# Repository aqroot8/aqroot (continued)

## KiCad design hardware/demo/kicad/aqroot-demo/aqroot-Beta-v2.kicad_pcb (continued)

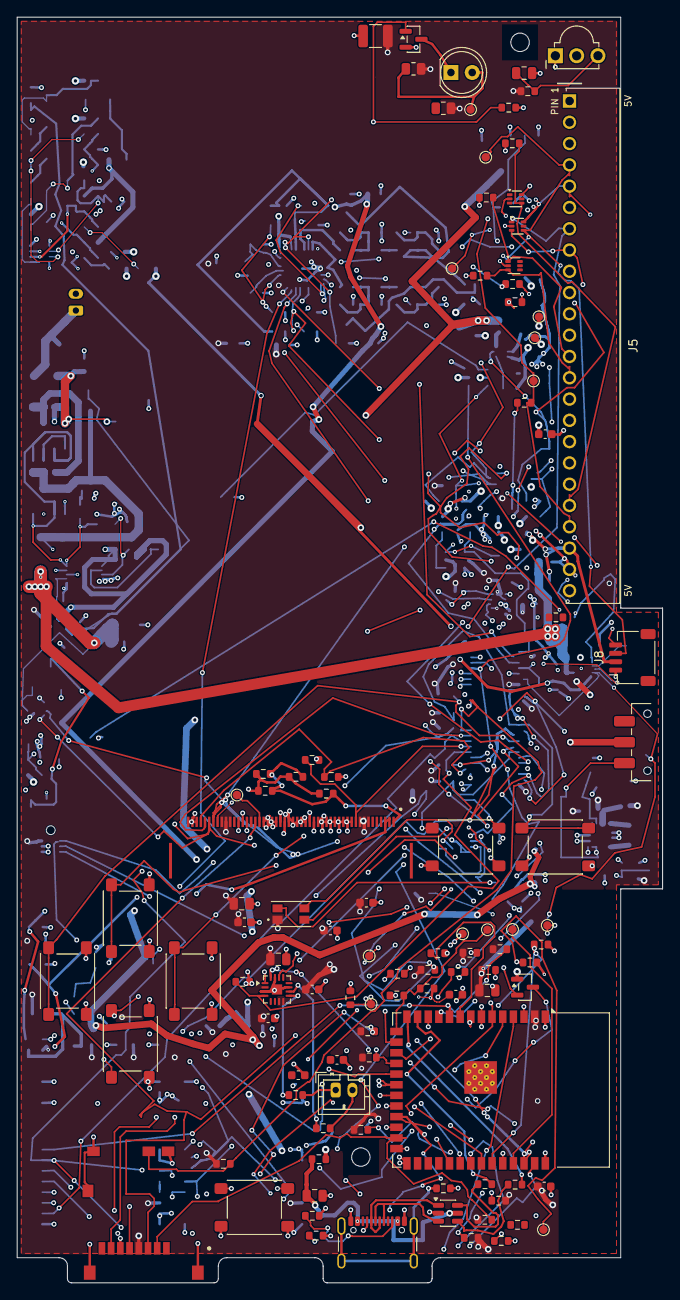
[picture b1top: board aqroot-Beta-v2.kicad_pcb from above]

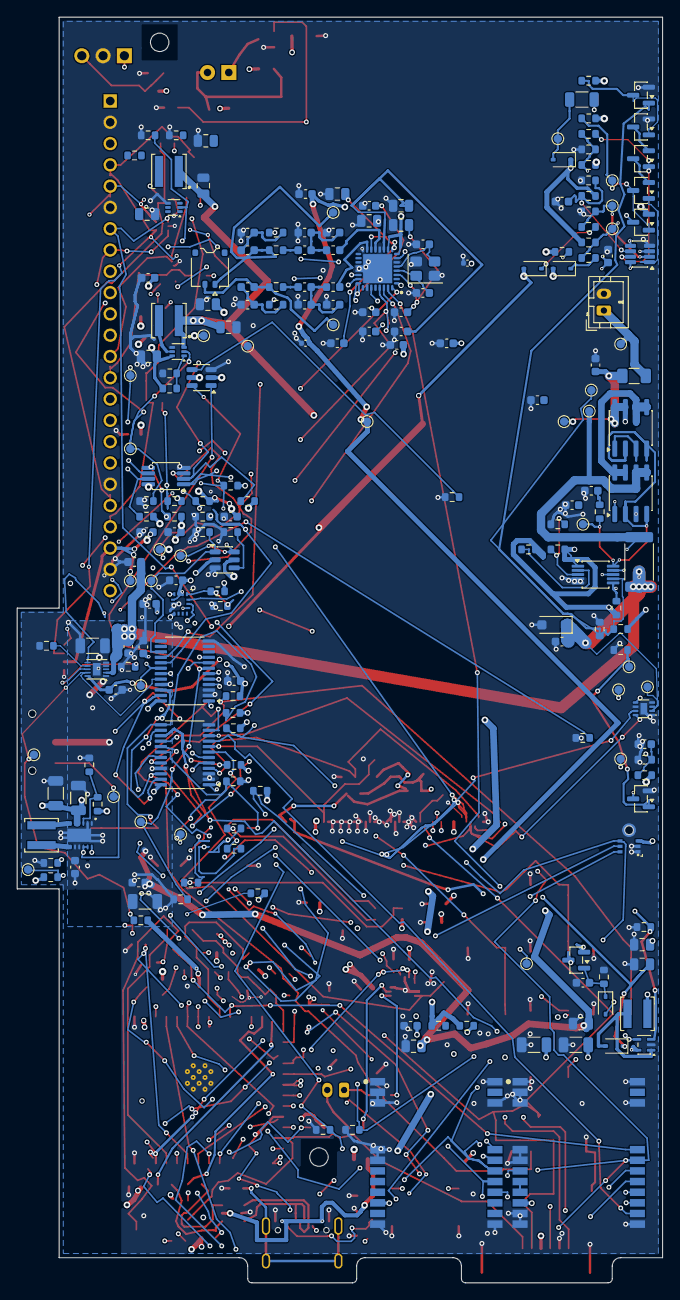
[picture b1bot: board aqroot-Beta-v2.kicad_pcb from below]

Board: 6 copper layers, 77.0 x 151.0 mm, 315 parts (211 on the bottom side), 177 nets.

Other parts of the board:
BOSS1, BOSS2: M2; MountingBoss_M2_NPTH

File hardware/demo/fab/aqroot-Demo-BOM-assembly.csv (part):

"Refs","Value","Footprint","Manufacturer","MPN","LCSC","Description","Qty","DNP"
"C1,C53,C56","1uF","Capacitor_SMD:C_0603_1608Metric","Samsung Electro-Mechanics","CL10A105KB8NNNC","C15849","Unpolarized capacitor","3",""
"C10","10uf","Capacitor_SMD:C_0805_2012Metric","Murata Electronics","GRM21BR61H106KE43L","C440198","Unpolarized capacitor","1",""
"C11","4.7uF","Capacitor_SMD:C_0805_2012Metric","Samsung Electro-Mechanics","CL21A475KAQNNNE","C1779","Unpolarized capacitor","1",""
"C12","22uF","Capacitor_SMD:C_1210_3225Metric","Samsung Electro-Mechanics","CL32B226KAJNNNE","C309062","Unpolarized capacitor","1",""
"C18,C19","100nF","Capacitor_SMD:C_0402_1005Metric","YAGEO","CC0402KRX7R8BB104","C105883","Unpolarized capacitor","2",""
"C2,C4,C5,C6,C7,C8,C9,C13,C14,C16,C17","100nF","Capacitor_SMD:C_0603_1608Metric","YAGEO","CC0603KRX7R9BB104","C14663","Unpolarized capacitor","11",""
"C20","4.7uF 10V X7R","Capacitor_SMD:C_0805_2012Metric","YAGEO","CC0805KKX7R8BB475","C354262","Unpolarized capacitor","1",""
"C23,C58,C59","1uF 25V X7R","Capacitor_SMD:C_0603_1608Metric","YAGEO","CC0603KRX7R8BB105","C106858","Unpolarized capacitor","3",""
"C24","10uF 25V X5R","Capacitor_SMD:C_0603_1608Metric","Murata","GRM188R61E106KA73D","C344022","Unpolarized capacitor","1",""
"C25,C37,C38,C62,C63,C67,C85","1uF 10V X7R","Capacitor_SMD:C_0603_1608Metric","YAGEO","CC0603KRX7R8BB105","C106858","Unpolarized capacitor","7",""
"C26,C27","10uF 10V X7R","Capacitor_SMD:C_1206_3216Metric","Murata Electronics","GRM31CR71E106KA12L","C77093","Unpolarized capacitor","2",""
"C28,C36,C39,C60,C61,C68","100nF X7R","Capacitor_SMD:C_0603_1608Metric","YAGEO","CC0603KRX7R9BB104","C14663","Unpolarized capacitor","6",""
"C29,C30,C31,C32","22uF 16V X7R","Capacitor_SMD:C_1206_3216Metric","CCTC","TCC1206X7R226K160HT","C22392398","Unpolarized capacitor","4",""
"C3,C15","10uF","Capacitor_SMD:C_0805_2012Metric","Murata Electronics","GRM21BR61H106KE43L","C440198","Unpolarized capacitor","2",""
"C33,C64,C83,C84","10uF 10V X7R","Capacitor_SMD:C_0805_2012Metric","YAGEO","CC0805KKX7R7BB106","C326595","Unpolarized capacitor","4",""
"C43","4.7uF 10V X5R","Capacitor_SMD:C_0805_2012Metric","Samsung Electro-Mechanics","CL21A475KAQNNNE","C1779","4.7uF","1",""
"C44","1uF","Capacitor_SMD:C_0805_2012Metric","Samsung Electro-Mechanics","CL21B105KBFNNNE","C28323","1uF","1",""
"C45,C47,C49,C51","2.2uF","Capacitor_SMD:C_0805_2012Metric","YAGEO","CC0805KKX7R9BB225","C125847","2.2uF","4",""
"C46,C48,C50,C54","10nF","Capacitor_SMD:C_0603_1608Metric","FH (Guangdong Fenghua Advanced Tech)","0603B103K500NT","C57112","10nF","4",""
"C52","1nF","Capacitor_SMD:C_0603_1608Metric","Samsung Electro-Mechanics","CL10B102KB8NNNC","C1588","1nF","1",""
"C55","2.2uF","Capacitor_SMD:C_0603_1608Metric","Samsung Electro-Mechanics","CL10A225KO8NNNC","C23630","Unpolarized capacitor","1",""
"C57","4.7nF 50V X7R","Capacitor_SMD:C_0603_1608Metric","FH (Guangdong Fenghua Advanced Tech)","0603B472K500NT","C53987","","1",""
"C65,C66","22uF 10V X7R","Capacitor_SMD:C_0805_2012Metric","Murata Electronics","GRM21BZ71A226ME15L","C907991","","2",""
"C69,C70","100pF 50V C0G TUNE","Capacitor_SMD:C_0603_1608Metric","Samsung Electro-Mechanics","CL10C101JB8NNNC","C14858","","2",""
"C71,C72","300pF 50V C0G TUNE","Capacitor_SMD:C_0603_1608Metric","Murata Electronics","GCM1885C2A301FA16J","C3837533","","2",""
"C73,C74","1.5nF 50V C0G TUNE","Capacitor_SMD:C_0603_1608Metric","Murata Electronics","GCM1885C2A152JA16D","C388906","","2",""
"C75,C77","27pF 50V C0G TUNE","Capacitor_SMD:C_0603_1608Metric","Murata Electronics","GQM1875C2E270FB12D","C2360423","","2",""
"C76,C78","620pF 50V C0G TUNE","Capacitor_SMD:C_0603_1608Metric","YAGEO","CC0603JRNPO9BN621","C325470","","2",""
"C79,C80","10pF 50V C0G TUNE","Capacitor_SMD:C_0603_1608Metric","Samsung Electro-Mechanics","CL10C100JB8NNNC","C1634","","2",""
"D1","TSAL6100","LED_THT:LED_D5.0mm","Vishay","TSAL6100","C111836","High-power 940 nm IR emitting diode, T-1 3/4","1",""
"D10,D11,D12,D14","BAT54WS","Diode_SMD:D_SOD-323","Diodes Incorporated","BAT54WS-7-F","C124205","","4",""
"D13","MHPA3528RGBCT","AQROOT_Beta:MEIHUA_MHPA3528RGBCT_PLCC4_3.5x2.8mm","MEIHUA","MHPA3528RGBCT","C409779","","1",""
"D2,D4,D5","TPD4E1B06DRLR","Package_TO_SOT_SMD:SOT-563","Texas Instruments","TPD4E1B06DRLR","C1972953","TI TPD4E1B06 4-channel ultra-low-leakage bidirectional ESD array, SOT-563","3",""
"D8","NSR0240","Diode_SMD:D_SOD-323","onsemi","NSR0240HT1G","C152519","Schottky barrier diode, 40V","1",""
"D9","PMEG2010AEH","Diode_SMD:D_SOD-123F","Nexperia","PMEG2010AEH,115","C110921","","1",""
"F1","5A one-shot 1206","Fuse:Fuse_1206_3216Metric","Littelfuse","0466005.NRHF","C57525","","1",""
"J1","FH69-50S-0.5SH","AQROOT_Beta:Hirose_FH69-50S-0.5SH","Hirose","FH69-50S-0.5SH","C25955556","EastRising ER-TFT035IPS-6 + ER-TPC035-6: 3.5in 320x480 IPS TFT (ILI9488) with FT6236 capacitive touch, one 50-pin 0.50mm bottom-contact FPC, mating Hirose FH69-50S-0.5SH","1",""
"J2","Molex_5025700893","AQROOT_Beta:Molex_5025700893","Molex","5025700893","C429846","Molex 5025700893 microSD card connector, push-push, with mechanical card detect","1",""
"J3","USB_C_Receptacle_USB2.0_16P","Connector_USB:USB_C_Receptacle_GCT_USB4105-xx-A_16P_TopMnt_Horizontal","GCT (Global Connector Technology)","USB4105-GF-A-120","C5184243","USB 2.0-only 16P Type-C Receptacle connector","1",""
"J5","COMMUNITY_PORT_1x24","AQROOT_Beta:Samtec_SSQ-124-02-G-S-RA","Samtec","SSQ-124-02-G-S-RA","C3323671","Samtec SSQ-124-02-G-S-RA 1x24 24-contact 2.54 mm female right-angle square-post socket strip, 20 uin gold, through-hole","1",""
"J6","JST-PH-2 SPEAKER","Connector_JST:JST_PH_B2B-PH-K_1x02_P2.00mm_Vertical","JST","B2B-PH-K-S(LF)(SN)","C131337","Generic connector, single row, 01x02, script generated (kicad-library-utils/schlib/autogen/connector/)","1",""
"J7","BM02B-ACHSS-GAN-ETF","Connector_JST:JST_ACH_BM02B-ACHSS-GAN-ETF_1x02-1MP_P1.20mm_Vertical","JST","BM02B-ACHSS-GAN-ETF(LF)(SN)","C5118738","","1",""
"J8","QWIIC_STEMMA_QT","Connector_JST:JST_SH_SM04B-SRSS-TB_1x04-1MP_P1.00mm_Horizontal","JST","SM04B-SRSS-TB(LF)(SN)","C160404","Qwiic / STEMMA QT I2C connector, JST SM04B-SRSS-TB(LF)(SN), SH series 1.0 mm pitch, 4 circuit, SIDE ENTRY, surface mount, body 6.0 x 4.25 mm, 1.0 A, 50 V AC/DC, -25 to +85 C, contact resistance 20 mOhm initial. ADDED AT FBV2-EXP-002 (D-238). PIN ORDER IS THE ECOSYSTEM STANDARD, NOT A CHOICE: 1 GND (black), 2 3.3 V (red), 3 SDA (blue), 4 SCL (yellow) - identical for SparkFun Qwiic and Adafruit STEMMA QT, so every cable in either ecosystem mates it. IT ADDS NO COMPONENT: it lands on the PROTECTED EXTERNAL segment at EXT_SDA / EXT_SCL, downstream of U16 TCA4307 and of the R47/R48 22 ohm series pair and at D2's TPD4E1B06 clamp, so it inherits the hot-swap buffer, the R49/R50 1.5 k pull-ups, the series resistance and the ESD array. POWER IS ACC_3V3_SW AND THAT IS ARCHITECTURAL, NOT A PREFERENCE: U16's own VCC is already ACC_3V3_SW and the pull-ups pull to it, so feeding the port from unswitched +3V3 would create a powered-device / unpowered-bus state and invite back-feeding through the accessory's ESD diodes. ACC_5V_SW IS NEVER EXPOSED HERE.","1",""
"L1","1.5uH","AQROOT_Beta:Coilcraft_XFL4020","Coilcraft","XFL4020-152MEC","C3033018","Inductor","1",""
"L3","4.7uH","AQROOT_Beta:Coilcraft_XFL4020","Coilcraft","XFL4020-472MEC","C5156236","4.7uH","1",""
"L4","1uH","AQROOT_Beta:Wurth_WE-MAPI_4030_74438357010","Wurth Elektronik","74438357010","C5542269","","1",""
"L5,L6","39nH TUNE","Inductor_SMD:L_0603_1608Metric","Murata Electronics","LQW18AN39NG80D","C2042966","","2",""
"MK1","DMM-4026-B-I2S","AQROOT_Beta:PUI_DMM-4026-B-I2S_4.0x3.0mm","PUI Audio","DMM-4026-B-I2S-R","C3171792","PUI Audio bottom-port MEMS I2S microphone, 7-pad, 4.0 x 3.0 x 1.0 mm","1",""
"Q1","AO3400A","Package_TO_SOT_SMD:SOT-23","Alpha & Omega Semiconductor","AO3400A","C20917","N-MOSFET transistor, gate/source/drain","1",""
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
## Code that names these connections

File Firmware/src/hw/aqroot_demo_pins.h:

#pragma once
// AQROOT Demo -- the MCU pin inventory, and the safe state every pin is parked
// in before any driver claims it.
//
// The point of the table is that it is EXHAUSTIVE.  `firmware_hw_map_contract`
// fails if any role the generator emits is missing from the hardware layer, so
// a board revision that adds a pin cannot reach an assembled unit with nothing
// in firmware deciding what that pin does at boot.
//
// THREE STRAPPING PINS CARRY SIGNALS AND ONE MORE IS NOT OURS AT ALL:
//   GPIO0  BOOT_N          R2 10k pull-up + SW1.  Input, and readable as a
//                          recovery button after boot.
//   GPIO3  BMI270_INT1     R110 10k pull-down holds the JTAG-source strap low
//                          through reset; R18 220R isolates the IMU driver.
//                          Input, never an output.
//   GPIO46 DISP_BL_PWM     must be LOW at reset (R108 10k to GND), which also
//                          leaves the backlight boost disabled.  Park it LOW
//                          and only then attach PWM.
//                          D-750 MADE LOW MEAN DARK.  The TPS61169 retains a
//                          DC path from +3V3 through L3/D8 to the panel LEDs
//                          in shutdown, and TI guarantees OFF only when the
//                          array's minimum Vf exceeds the maximum VIN -- this
//                          panel is 2.9-3.2 V on a 3.3 V rail, so it did not.
//                          Q11 (Vishay SQ2364EES) now sits in the panel
//                          cathode return, its gate driven from this line
//                          through D14 / C85 / R132, and R108 holds the line
//                          low, so a firmware crash, a GPIO left in
//                          high-impedance and a reset all leave the screen
//                          dark.  PWM on this pin gates the LED current
//                          directly instead of restarting the converter.
//   GPIO45 VDD_SPI strap   has NO firmware role and is deliberately absent
//                          from this table.  R111 and TP1 are its only load.

#include <stdint.h>

#include "aqroot_demo_board.h"

namespace aqroot {

enum class PinMode : uint8_t {
  InputFloating,     // driven by an external device, no MCU pull
  InputPullUp,       // MCU pull-up needed; nothing external defines the level
  OutputLow,         // park low
  OutputHigh,        // park high
  Peripheral,        // owned by SPI/I2C/I2S/USB/UART -- do not touch as a GPIO
};

struct PinEntry {
  const char *name;
  uint8_t gpio;
  PinMode mode;
};

// The whole of U1's firmware-visible surface, in board-pad order.
static const PinEntry kPins[] = {
    // ---- SPI-B: CC1101 (U7) + SX1262 (U8) + ST25R3916 (U9), one TX at a time
    {"SPI_B_SCK", AQROOT_PIN_SPI_B_SCK, PinMode::Peripheral},
    {"SPI_B_MOSI", AQROOT_PIN_SPI_B_MOSI, PinMode::Peripheral},
    {"SPI_B_MISO", AQROOT_PIN_SPI_B_MISO, PinMode::Peripheral},
    {"CC1101_CS_N", AQROOT_PIN_CC1101_CS_N, PinMode::OutputHigh},
    {"CC1101_GDO0", AQROOT_PIN_CC1101_GDO0, PinMode::InputFloating},
    {"SX1262_CS_N", AQROOT_PIN_SX1262_CS_N, PinMode::OutputHigh},
    {"SX1262_BUSY", AQROOT_PIN_SX1262_BUSY, PinMode::InputFloating},
    {"NFC_CS_N", AQROOT_PIN_NFC_CS_N, PinMode::OutputHigh},
    {"NFC_IRQ", AQROOT_PIN_NFC_IRQ, PinMode::InputFloating},
    // ---- SPI-A: display (J1) + microSD (J2).  MISO reaches the CARD ONLY.
    {"SPI_A_SCK", AQROOT_PIN_SPI_A_SCK, PinMode::Peripheral},
    {"SPI_A_MOSI", AQROOT_PIN_SPI_A_MOSI, PinMode::Peripheral},
    {"SPI_A_MISO", AQROOT_PIN_SPI_A_MISO, PinMode::Peripheral},
    {"DISP_CS_N", AQROOT_PIN_DISP_CS_N, PinMode::OutputHigh},
    {"DISP_DC", AQROOT_PIN_DISP_DC, PinMode::OutputLow},
    {"DISP_BL_PWM", AQROOT_PIN_DISP_BL_PWM, PinMode::OutputLow},
    {"SD_CS_N", AQROOT_PIN_SD_CS_N, PinMode::OutputHigh},
    // ---- I2C, I2S, IR
    {"I2C_SDA", AQROOT_PIN_I2C_SDA, PinMode::Peripheral},
    {"I2C_SCL", AQROOT_PIN_I2C_SCL, PinMode::Peripheral},
    {"I2S_BCLK", AQROOT_PIN_I2S_BCLK, PinMode::Peripheral},
    {"I2S_LRCLK", AQROOT_PIN_I2S_LRCLK, PinMode::Peripheral},
    {"I2S_SPK_DOUT", AQROOT_PIN_I2S_SPK_DOUT, PinMode::Peripheral},
    {"I2S_MIC_DIN", AQROOT_PIN_I2S_MIC_DIN, PinMode::Peripheral},
    {"IR_TX", AQROOT_PIN_IR_TX, PinMode::OutputLow},
    {"IR_RX", AQROOT_PIN_IR_RX, PinMode::InputFloating},
    // ---- straps, wake, expansion, console
    {"BOOT_N", AQROOT_PIN_BOOT_N, PinMode::InputFloating},
    {"BMI270_INT1", AQROOT_PIN_BMI270_INT1, PinMode::InputFloating},
    {"WAKE_INT_N", AQROOT_PIN_WAKE_INT_N, PinMode::InputFloating},
    {"NATIVE_A", AQROOT_PIN_NATIVE_A, PinMode::InputPullUp},
    {"NATIVE_B", AQROOT_PIN_NATIVE_B, PinMode::InputPullUp},
    {"UART0_TXD", AQROOT_PIN_UART0_TXD, PinMode::Peripheral},
};

static const size_t kPinCount = sizeof(kPins) / sizeof(kPins[0]);

#ifdef ARDUINO
#include <Arduino.h>

// Park every firmware-visible pin.  Call FIRST, before any driver.  Peripheral
// pins are left alone -- claiming them as GPIO here would fight the SPI/I2S/USB
// controllers that take them moments later.
inline void parkAllPins() {
  for (size_t i = 0; i < kPinCount; ++i) {
    switch (kPins[i].mode) {
      case PinMode::Peripheral:
        break;
      case PinMode::InputFloating:
        pinMode(kPins[i].gpio, INPUT);
        break;
      case PinMode::InputPullUp:
        pinMode(kPins[i].gpio, INPUT_PULLUP);
        break;
      case PinMode::OutputLow:
        pinMode(kPins[i].gpio, OUTPUT);
        digitalWrite(kPins[i].gpio, LOW);
        break;
      case PinMode::OutputHigh:
        pinMode(kPins[i].gpio, OUTPUT);
        digitalWrite(kPins[i].gpio, HIGH);
        break;
    }
  }
}
#endif  // ARDUINO

}  // namespace aqroot

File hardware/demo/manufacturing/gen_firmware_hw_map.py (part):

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# own GPIO (`IO4`, `IO45`, ...).  These four name the FUNCTION Espressif
# silkscreens on the module, and the GPIO behind each is fixed silicon.  Three
# of the four are corroborated by this board's own net names -- `RXD0` carries
# `/IR_RX_GPIO44`, and `USB_D-`/`USB_D+` carry `/USB_D_MCU_N`/`_P`, which are
# the ESP32-S3's native USB pins and exist nowhere else on the die.
MODULE_PIN_ALIASES = {
    "USB_D-": ("IO19", "native USB D- (USB Serial/JTAG)"),
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             note="shared SPI-B: CC1101 + SX1262 + ST25R3916"),
    5:  dict(role="SPI_B_MOSI", kind="BUS", net="/SPI_B_MOSI", note="shared SPI-B"),
    6:  dict(role="SPI_B_MISO", kind="BUS", net="/SPI_B_MISO", note="shared SPI-B"),
    7:  dict(role="CC1101_CS_N", kind="PIN", net="/CC1101_CS_N",
             note="433 MHz E07 chip select, active low"),
    8:  dict(role="CC1101_GDO0", kind="PIN", net="/CC1101_GDO0",
             note="433 MHz packet/sync interrupt; GDO2 is NOT wired on this board"),
    9:  dict(role="IR_TX", kind="PIN", net="/IR_TX_GPIO16",
             note="drives Q1 gate through R22 100R; R23 100k gate pull-down; ACTIVE HIGH"),
    10: dict(role="SX1262_CS_N", kind="PIN", net="/SX1262_CS_N",
             note="915 MHz E22 chip select, active low"),
    11: dict(role="NFC_IRQ", kind="PIN", net="/NFC_IRQ",
             note="ST25R3916 IRQ, push-pull, ACTIVE HIGH; no external pull"),
    12: dict(role="SX1262_BUSY", kind="PIN", net="/SX1262_BUSY",
             note="SX1262 BUSY; must be low before any command"),
    13: dict(role=None, kind="FIXED", net="/USB_D_MCU_N",
             note="native USB D-, 22R series; owned by the USB Serial/JTAG peripheral"),
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                 "GPIO46 must be LOW at reset.  R108 10k to GND does that AND "
                 "leaves the backlight boost U17 disabled until firmware drives it"),
             note="U17 TPS61169 WLED boost enable / PWM brightness through R109 0R"),
    17: dict(role="NFC_CS_N", kind="PIN", net="/NFC_CS_N",
             note="ST25R3916 chip select, active low"),
    18: dict(role="DISP_CS_N", kind="PIN", net="/DISP_CS_N",
             note="display chip select, active low"),
    19: dict(role="SPI_A_MOSI", kind="BUS", net="/SPI_A_MOSI",
             note="shared SPI-A: display + microSD"),
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    21: dict(role="SPI_A_MISO", kind="BUS", net="/SPI_A_MISO",
             note="shared SPI-A -- reaches the microSD ONLY.  R112 0R is DNP, so the "
                  "display SDO is ISOLATED and the panel CANNOT be read back"),
    22: dict(role="DISP_DC", kind="PIN", net="/DISP_DC",
             note="display data/command"),
    23: dict(role="WAKE_INT_N", kind="PIN", net="/WAKE_INT_N",
             note="shared open-drain wake line: U2./INT, U3./INT and the accessory "
                  "attention path through Q10.  R3 10k pull-up.  LEVEL sensitive, "
                  "ACTIVE LOW, RTC-capable for deep-sleep wake"),
    24: dict(role="NATIVE_B", kind="PIN", net="/NATIVE_B",
             note="Community Port native GPIO B, J5.8 through R62 100R, D2 ESD"),
    25: dict(role="SD_CS_N", kind="PIN", net="/SD_CS_N",
             note="microSD chip select, active low"),
    26: dict(role=None, kind="STRAP", net="/02_MCU_CORE/GPIO45_VDDSPI_STRAP",
             strap_level=0, strap_part="R111", strap_why=(
                 "GPIO45 selects VDD_SPI.  R111 10k to GND is the ONLY load besides "
                 "TP1.  Firmware must never claim this pin"),
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             note="IO36 -- octal PSRAM, unusable, left NC"),
    30: dict(role=None, kind="NC", net=None,
             note="IO37 -- octal PSRAM, unusable, left NC"),
    31: dict(role="NATIVE_A", kind="PIN", net="/NATIVE_A",
             note="Community Port native GPIO A, J5.7 through R61 100R, D2 ESD"),
    32: dict(role="I2S_BCLK", kind="BUS", net="/I2S_BCLK",
             note="shared I2S bit clock: MAX98357A out + DMM-4026 mic in"),
    33: dict(role="I2S_LRCLK", kind="BUS", net="/I2S_LRCLK", note="shared I2S word clock"),
    34: dict(role="I2S_SPK_DOUT", kind="PIN", net="/I2S_SPK_DOUT",
             note="I2S data to the MAX98357A"),
    35: dict(role="I2S_MIC_DIN", kind="PIN", net="/I2S_MIC_DIN",
             note="I2S data from the DMM-4026-B-I2S MEMS microphone"),
    36: dict(role="IR_RX", kind="PIN", net="/IR_RX_GPIO44",
             note="TSOP38238 demodulated output, ACTIVE LOW, internally pulled up; "
                  "Vs fed through R21 100R + C11"),
    37: dict(role="UART0_TXD", kind="FIXED", net="/02_MCU_CORE/UART0_TXD_DBG",
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                             "the PCAL powers up high-impedance.  This is the SECOND "
                             "of D-186's two independent series disconnects; the "
                             "first is ACC_5V_BOOST_EN on U3.P13"),
            "P04": dict(role="XGPIO4", net="/XGPIO4", dir="IN",
                        active="HIGH", pull="UP", idle_basis="internal_pull",
                        irq="MASKED",
                        note="public Community-Port expansion GPIO, J5.13 through "
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                             "100k pull-up so an empty header reads a defined 1.  "
                             "MASKED is MX-9: an accessory must not be able to hold "
                             "the shared wake line and starve the buttons"),
            "P05": dict(role="XGPIO5", net="/XGPIO5", dir="IN",
                        active="HIGH", pull="UP", idle_basis="internal_pull",
                        irq="MASKED",
                        note="public Community-Port expansion GPIO, J5.14 through "
                             "R56 100R, D4 ESD.  See XGPIO4"),
            "P06": dict(role="SPARE_U3_P06", net=None, dir="IN", active="HIGH",
                        pull="UP", idle_basis="internal_pull", irq="MASKED",
                        note="NC-DEMO spare.  No external part at all, so the internal "
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
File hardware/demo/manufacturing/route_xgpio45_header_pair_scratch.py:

#!/usr/bin/env python3
"""Route and fully gate the retained Demo XGPIO4/5 connector-side trees."""

import argparse
import hashlib
import json
import subprocess
import sys
import tempfile
from collections import Counter
from pathlib import Path

import pcbnew

ROOT = Path(__file__).resolve().parents[3]
BOARD = ROOT / "hardware/demo/kicad/aqroot-demo/aqroot-Beta-v2.kicad_pcb"
LOCAL = Path(__file__).with_name("route_local_two_pad.py")
LEDGER = Path(__file__).with_name("routing_ledger.py")
NETS = ("/09_COMMUNITY_HEADER/XGPIO4_HDR", "/09_COMMUNITY_HEADER/XGPIO5_HDR")
ORDERS = {
    "xgpio4-first": ("XGPIO4_HDR_TVS", "XGPIO4_HDR_J5", "XGPIO5_HDR_TVS", "XGPIO5_HDR_J5"),
    "xgpio5-first": ("XGPIO5_HDR_TVS", "XGPIO5_HDR_J5", "XGPIO4_HDR_TVS", "XGPIO4_HDR_J5"),
}
ACCEPTED = {"lib_footprint_issues", "hole_clearance", "solder_mask_bridge"}


def sha256(path):
    return hashlib.sha256(path.read_bytes()).hexdigest()


def copper(board):
    result = Counter()
    for item in board.GetTracks():
        if item.GetClass() == "PCB_VIA":
            key = (item.GetNetname(), "VIA", item.GetWidth(), item.GetDrillValue(),
                   item.GetPosition().x, item.GetPosition().y)
        else:
            ends = sorted(((item.GetStart().x, item.GetStart().y),
                           (item.GetEnd().x, item.GetEnd().y)))
            key = (item.GetNetname(), item.GetLayerName(), item.GetWidth(), *ends)
        result[key] += 1
    return result


def main():
    parser = argparse.ArgumentParser()
    parser.add_argument("--launch-order", choices=sorted(ORDERS), default="xgpio4-first")
    parser.add_argument("--candidate", type=Path)
    parser.add_argument("--promote", action="store_true")
    args = parser.parse_args()
    before_sha = sha256(BOARD)
    baseline = copper(pcbnew.LoadBoard(str(BOARD)))
    with tempfile.TemporaryDirectory(prefix="aqroot-demo-xgpio45-header-") as temporary:
        work = Path(temporary)
        scratch = work / BOARD.name
        for suffix in (".kicad_pcb", ".kicad_dru", ".kicad_pro"):
            scratch.with_suffix(suffix).write_bytes(BOARD.with_suffix(suffix).read_bytes())
        routes = []
        for name in ORDERS[args.launch_order]:
            run = subprocess.run([sys.executable, str(LOCAL), name, "--route", str(scratch)],
                                 check=True, text=True, capture_output=True)
            routes.append(json.loads(run.stdout))
        drc = work / "drc.json"
        checked = subprocess.run([
            "kicad-cli", "pcb", "drc", "--refill-zones", "--save-board",
            "--format", "json", "--units", "mm", "--severity-all",
            "--schematic-parity", "-o", str(drc), str(scratch),
        ], text=True, capture_output=True)
        violations = json.loads(drc.read_text()).get("violations", [])
        types = Counter(v.get("type", "unknown") for v in violations)
        attributable = [v for v in violations if v.get("type") not in ACCEPTED]
        after = copper(pcbnew.LoadBoard(str(scratch)))
        removed, added = baseline - after, after - baseline
        wrong = [list(item) for item in added if item[0] not in NETS]
        ledger_path = work / "ledger.json"
        subprocess.run([sys.executable, str(LEDGER), "--board", str(scratch),
                        str(ledger_path)], check=True, stdout=subprocess.DEVNULL)
        ledger = json.loads(ledger_path.read_text())
        rows = {r["net"]: r for r in ledger["nets"] if r["net"] in NETS}
        promotion = (all(r["result"].get("ok") for r in routes)
                     and all(rows[n]["open_edges"] == 0 for n in NETS)
                     and not attributable and not removed and not wrong)
        candidate = scratch.read_bytes()
        if args.candidate and promotion:
            args.candidate.write_bytes(candidate)
        if args.promote:
            if not promotion or sha256(BOARD) != before_sha:
                raise RuntimeError("refuse promotion: gate failed or authority changed")
            BOARD.write_bytes(candidate)
        report = {
            "schema": 1, "authoritative_board_sha256": before_sha,
            "authoritative_unchanged": sha256(BOARD) == before_sha,
            "launch_order": args.launch_order, "routes": routes,
            "drc_exit": checked.returncode, "drc_types": dict(types),
            "attributable_drc": attributable,
            "removed_accepted_copper_items": sum(removed.values()),
            "added_items": sum(added.values()), "wrong_net_additions": wrong,
            "target_open_edges": {n: rows[n]["open_edges"] for n in NETS},
            "connectivity": ledger["connectivity"], "promotion_candidate": promotion,
            "candidate_sha256": hashlib.sha256(candidate).hexdigest(),
        }
    print(json.dumps(report, indent=2, sort_keys=True))
    return 0 if promotion else 2


if __name__ == "__main__":
    raise SystemExit(main())
